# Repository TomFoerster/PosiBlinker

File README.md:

# PosiBlinker
A small circuit that utilizes the positionlight of a motorbike as a turnsignal.

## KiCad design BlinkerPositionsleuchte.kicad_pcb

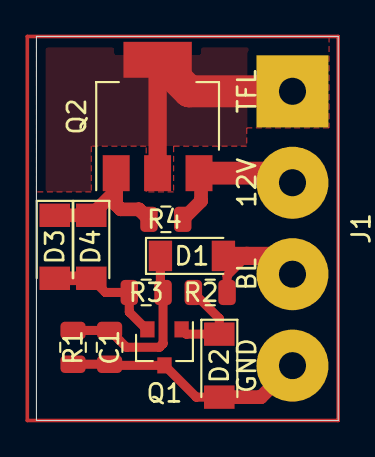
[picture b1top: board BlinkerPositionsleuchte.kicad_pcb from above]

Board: 2 copper layers, 16.8 x 21.3 mm, 12 parts (0 on the bottom side), 8 nets.

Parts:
C1: 500n; C_0805_2012Metric
D1, D3: D; D_MiniMELF
D2, D4: 7V; D_MiniMELF
J1: Conn_01x04_Male; SolderWirePad_1x04_P5.08mm_Drill1.5mm
Q1: Q_NMOS_GDS; SOT-23
Q2: Q_PMOS_GDS; SOT-223-3_TabPin2
R1: 2MEG; R_0805_2012Metric
R2, R3: 10k; R_0805_2012Metric
R4: 10M; R_0805_2012Metric

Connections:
12V: J1.2, Q2.3, R4.1
BL: D1.2, J1.3, R2.2
GND: C1.2, D2.2, J1.4, Q1.3, R1.2
unnamed: C1.1, D1.1, R1.1, R3.2
unnamed: D2.1, Q1.1, R2.1
unnamed: D3.1, D4.1, Q2.1, R4.2
unnamed: D3.2, D4.2, Q1.2, R3.1
TFL_Out: J1.1, Q2.2

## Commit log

2019-04-11 init
2019-04-11 Redesign auf pmos
2019-04-12 Layout fertig
